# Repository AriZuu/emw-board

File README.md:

EMW3165 sensor board
====================

Kicad stuff for EMW3165 based sensor board v2. This small
board has:

- EMW3165 module
- Connector for 1-wire sensors
- SWD connector for programming
- Two alternative power supplies (solder only one):
  - MCP1640 step-up converter, provides 3.3V from 2 AA batteries
  - MAX604 LDO regulator, provides 3.3V from 3 AAA batteries or from console FTDI

I have written two firmware alternatives for board. First 
is [emw-meter][1], which displays temperatures and house power usage. 
Second is [emw-sensor][2], which uses 1-wire devices to measure temperature
and send it to MQTT server.

This is Open Source Hardware, licensed under [CC-BY 4.0][3].
There are [some notes about the board][4] in my blog.

[1]: https://github.com/AriZuu/emw-meter
[2]: https://github.com/AriZuu/emw-sensor
[3]: https://creativecommons.org/licenses/by/4.0/
[4]: http://stonepile.fi/1-wire-wifi-sensor/

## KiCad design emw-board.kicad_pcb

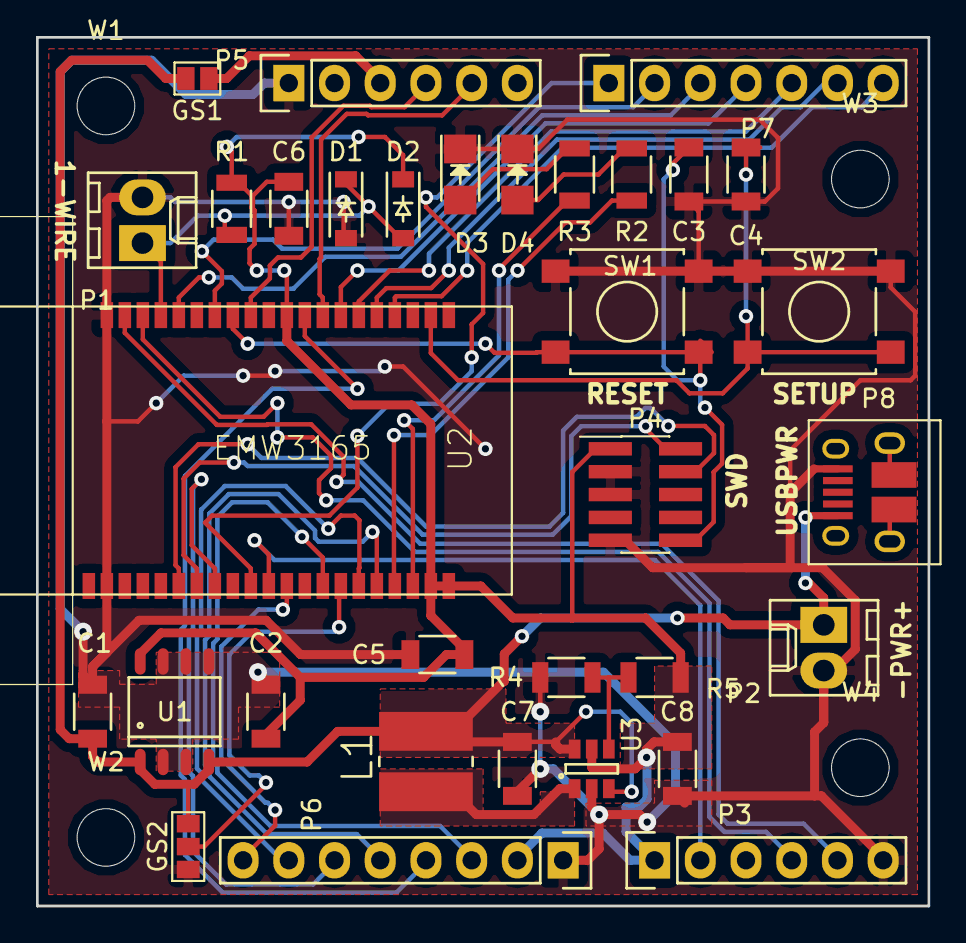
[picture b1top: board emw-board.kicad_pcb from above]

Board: 2 copper layers, 49.5 x 48.3 mm, 37 parts (0 on the bottom side), 34 nets.

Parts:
C1, C2: 10uF; C_1206
C3, C4, C5, C6: 100nF; C_1206
C7: 4.7u; C_1206
C8: 10u; C_1206
D1, D2: 1N4148; SOD-123
D3, D4: LED; LED_1206
GS1: GS2
GS2: GS3
L1: SD25-4R7-R; INDM5252X250N
P1: 1WIRE; Molex_KK-6410-02_02x2.54mm_Straight
P2: BATT; Molex_KK-6410-02_02x2.54mm_Straight
P3: CONN_01X06; Pin_Header_Straight_1x06
P4: SWDN; swd_connector_2x05_Pitch1.27mm_SMD
P5: CONS; Pin_Header_Straight_1x06
P6: OLED; Pin_Header_Straight_1x08
P7: CONN_01X07; Pin_Header_Straight_1x07
P8: USB_OTG; USB_Micro-B_10103594-0001LF
R1: 4.7K; R_1206
R2, R3: 270; R_1206
R4: 562K; R_1206
R5: 976K; R_1206
SW1, SW2: B3S-1000; SW_SPST_B3S-1000
U1: MAX604CSA; SO-8
U2: EMW3165
U3: MCP1640; SOT-23-6
W1, W2, W3, W4: TEST_1P; MountingHole_3.2mm_M3

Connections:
+3V3: C2.1, C5.1, C6.1, C8.1, D2.1, P3.1, P4.1, P6.2, R1.1, R5.1, U1.8, U2.10, U2.39, U2.40, U3.5
+BATT: C1.1, C7.1, GS1.2, GS2.1, L1.2, P2.1, P8.1, U1.1, U1.4, U3.3, U3.6
CONS_RX: P5.4, U2.12
CONS_TX: P5.5, U2.8
GND: C1.2, C2.2, C3.2, C4.2, C5.2, C6.2, C7.2, C8.2, D1.2, D3.1, D4.1, GS2.3, P1.2, P2.2, P3.6, P4.3, P4.5, P4.9, P5.1, P6.1, P8.5, R4.2, SW1.1, SW2.1, U1.2, U1.3, U1.5, U1.6, U1.7, U2.20, U2.21, U3.2
unnamed: C3.1, P4.10, SW1.2, U2.13
unnamed: D1.1, D2.2, P1.1, R1.2, U2.17
unnamed: D3.2, R3.1
unnamed: D4.2, R2.1
unnamed: GS1.1, P5.3
unnamed: GS2.2, U2.34
unnamed: L1.1, U3.1
unnamed: P4.2, U2.26
unnamed: P4.4, U2.25
unnamed: R2.2, U2.37
unnamed: R3.2, U2.38
unnamed: R4.1, R5.2, U3.4
OLED_CS: P6.8, U2.31
OLED_DC: P6.6, U2.27
OLED_RST: P6.5, U2.36
PA0: P7.2, U2.14
PA10: P7.1, U2.29
PB6: P3.2, U2.30
PB9: P3.4, U2.18
PB12: P3.5, U2.19
PC13: P7.3, U2.16
SETUP: C4.1, SW2.2, U2.2
SPI1_CLK: P7.5, U2.6
SPI1_CS: P7.6, U2.5
SPI1_MISO: P7.4, U2.7
SPI1_MOSI: P7.7, U2.4
SPI4_CLK: P6.3, U2.33
SPI4_MISO: P6.7, U2.35
SPI4_MOSI: P6.4, U2.9

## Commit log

2016-08-07 Initial commit.
2017-02-24 Fix ERC errors.
2017-02-25 ADC connection to VBAT. Replace SWD connector with smaller one.
2017-02-25 Reposition buttons. New SWD connector. Reposition power connector.
2017-02-26 Add CC BY 4.0 license.
2017-02-26 Add OSH logo.
2017-02-26 Update readme.
2017-02-26 Fix typo in links.
2017-02-26 Add copper pours.
2017-02-26 Regenerate copper pours.
2017-03-01 Move power and 1-wire connector so that right-angled type can also be used.
2017-03-02 Add seeedstudio order files.
2017-03-02 Typo fix.
2017-03-02 Add blog link.
2017-05-20 Rotate 1-wire connector.
2017-05-20 Fix swd connector placing.
2017-05-21 Add BOM info.
2017-05-21 Regenerated seeed order files.
2017-05-21 Cleanup some tracks.
2017-05-21 Update seeed order files.
2017-05-21 Remove old silkscreen text for unconnected pin.
2017-05-23 Add solder jumpers for selecting power from ftdi console and batter level measurement enable/disable.
2017-05-25 Add micro-usb connector (for power only).
2017-05-25 Upgrade to kicad 4.0.6.
